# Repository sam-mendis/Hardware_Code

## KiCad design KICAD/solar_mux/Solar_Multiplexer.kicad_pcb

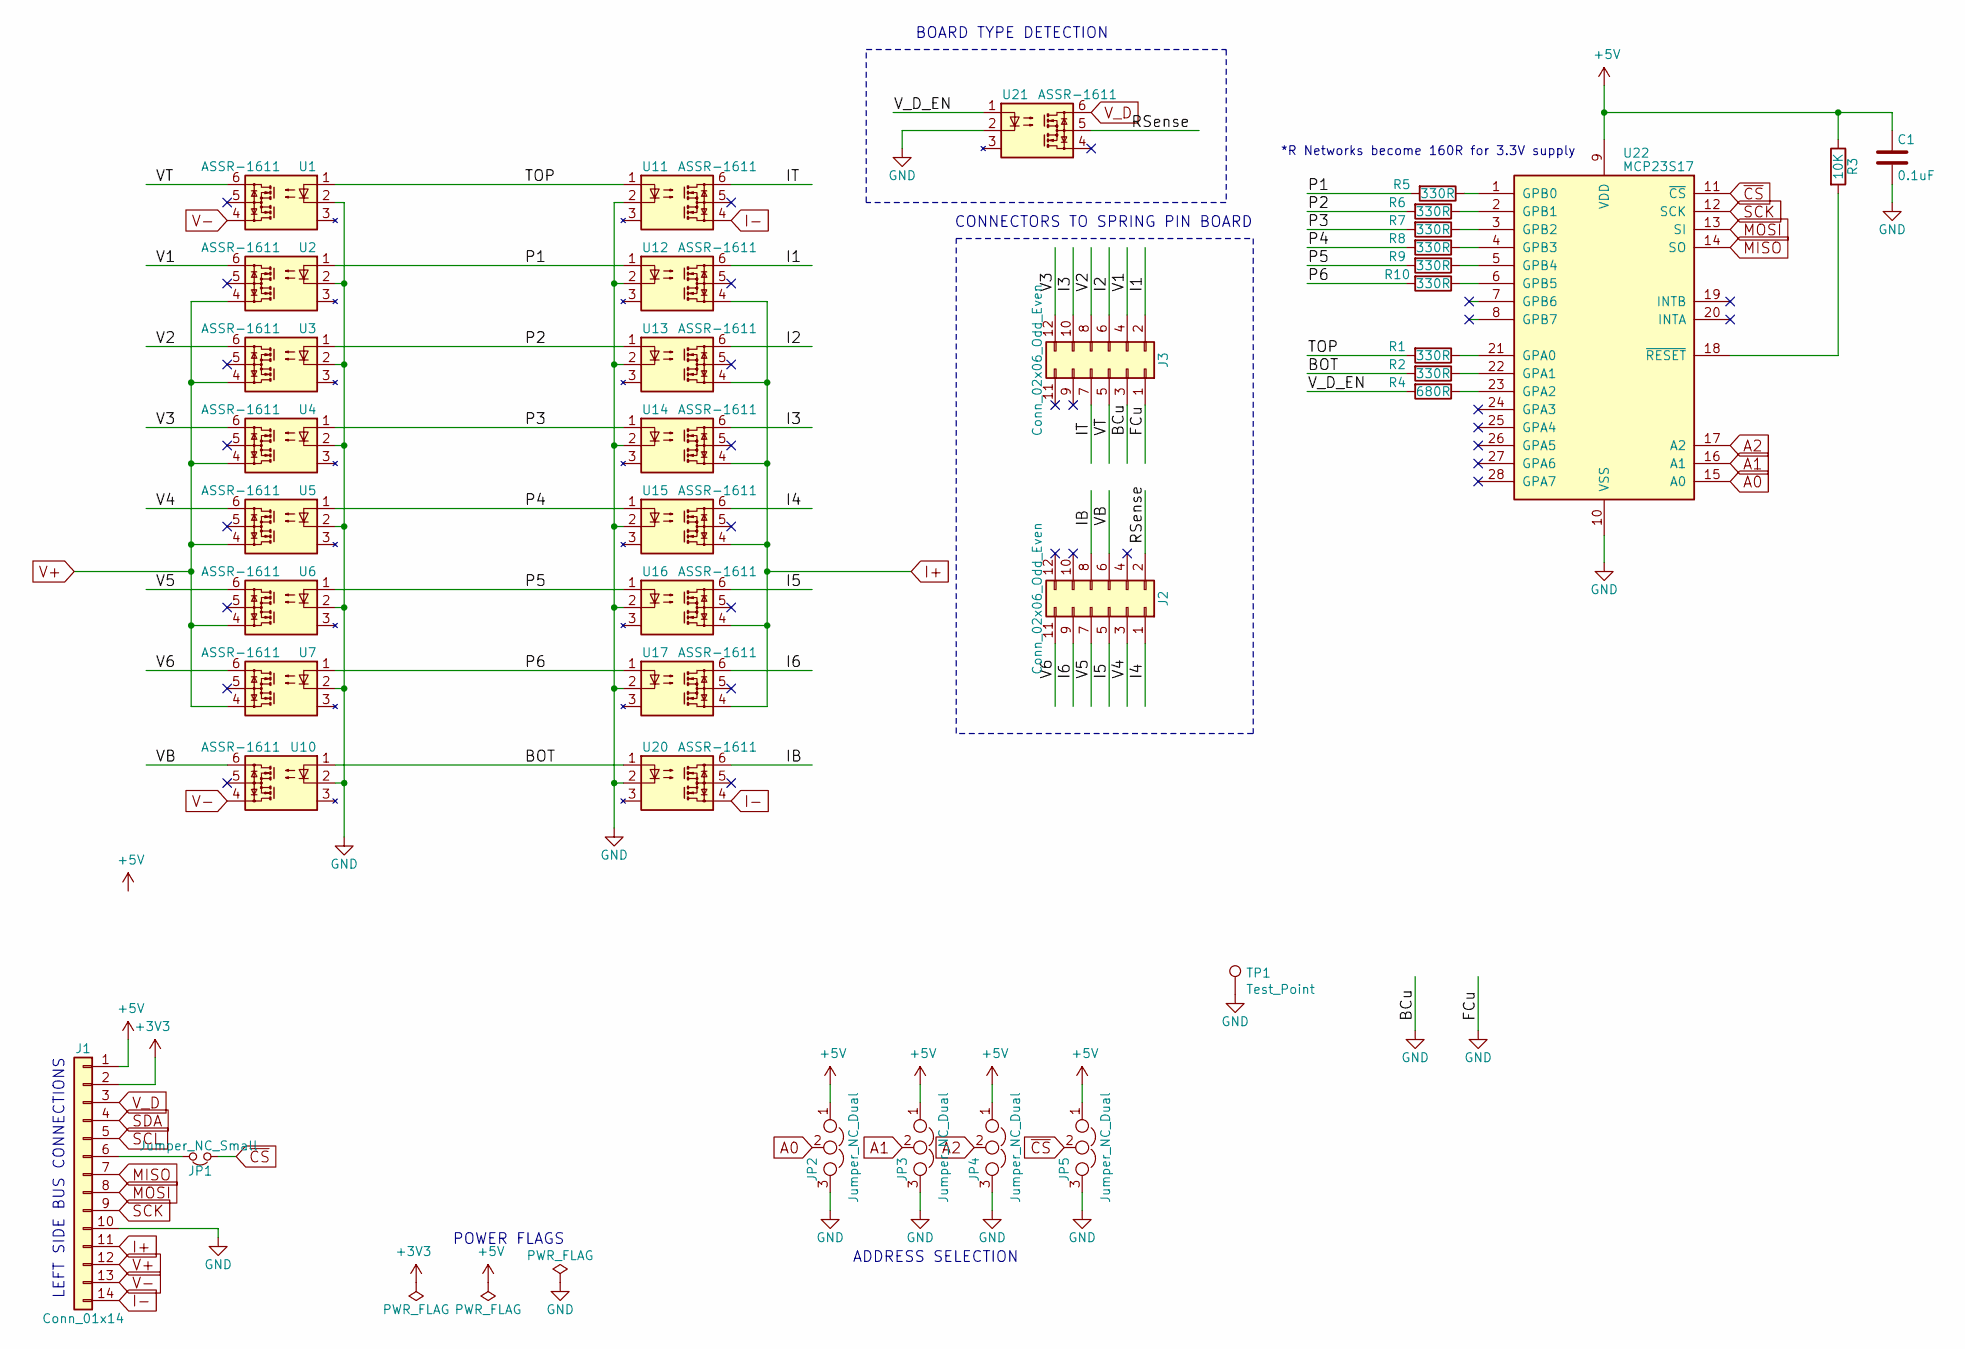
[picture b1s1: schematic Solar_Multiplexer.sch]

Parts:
C1: 0.1uF; CP_Radial_D8.0mm_P2.50mm; farnellCode 1759312
J1: Conn_01x14; PinHeader_1x14_P2.54mm_Vertical; farnellCode 2037821
J2: Conn_02x06_Odd_Even; PinHeader_2x06_P2.54mm_Vertical
J3: Conn_02x06_Odd_Even; PinHeader_2x06_P2.54mm_Vertical; FarnellPart 1930232
JP1: Jumper_NC_Small; SolderJumper-2_P1.3mm_Open_RoundedPad1.0x1.5mm
JP2, JP3, JP4, JP5: Jumper_NC_Dual; SolderJumper-3_P1.3mm_Open_RoundedPad1.0x1.5mm_NumberLabels
R1, R2, R5, R6, R7, R8, R9, R10: 330R; R_Axial_DIN0309_L9.0mm_D3.2mm_P15.24mm_Horizontal; farnellCode 2073607
R3: 10K; R_Axial_DIN0309_L9.0mm_D3.2mm_P15.24mm_Horizontal; farnellCode 2826357
R4: 680R; R_Axial_DIN0309_L9.0mm_D3.2mm_P15.24mm_Horizontal; farnellCode 2694489
TP1: Test_Point; TestPoint_Pad_2.5x2.5mm; farnell code 2293786
U1, U2, U3, U4, U5, U6, U7, U10, U11, U12, U13, U14, U15, U16, U17, U20, U21: ASSR-1611; DIP-6_W7.62mm; farnellCode 1708441
U22: MCP23S17; DIP-28_W7.62mm; farnellCode 1292238

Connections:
+3V3: J1.2
+5V: C1.1, J1.1, JP2.1, JP3.1, JP4.1, JP5.1, R3.1, U22.9 (VDD)
/BOT: R2.2, U10.1, U20.1
/I1: J3.2, U12.6
/I2: J3.6, U13.6
/I3: J3.10, U14.6
/I4: J2.1, U15.6
/I5: J2.5, U16.6
/I6: J2.9, U17.6
/IB: J2.8, U20.6
/IT: J3.7, U11.6
/P1: R5.2, U2.1, U12.1
/P2: R6.2, U3.1, U13.1
/P3: R7.2, U4.1, U14.1
/P4: R8.2, U5.1, U15.1
/P5: R9.2, U6.1, U16.1
/P6: R10.2, U7.1, U17.1
/RSense: J2.2, U21.5
/TOP: R1.2, U1.1, U11.1
/V1: J3.4, U2.6
/V2: J3.8, U3.6
/V3: J3.12, U4.6
/V4: J2.3, U5.6
/V5: J2.7, U6.6
/V6: J2.11, U7.6
/VB: J2.6, U10.6
/VT: J3.5, U1.6
/V_D_EN: R4.2, U21.1
A0: JP2.2, U22.15 (A0)
A1: JP3.2, U22.16 (A1)
A2: JP4.2, U22.17 (A2)
GND: C1.2, J1.10, J3.1, J3.3, JP2.3, JP3.3, JP4.3, JP5.3, TP1.1, U1.2, U2.2, U3.2, U4.2, U5.2, U6.2, U7.2, U10.2, U11.2, U12.2, U13.2, U14.2, U15.2, U16.2, U17.2, U20.2, U21.2, U22.10 (VSS)
I+: J1.11, U12.4, U13.4, U14.4, U15.4, U16.4, U17.4
I-: J1.14, U11.4, U20.4
MISO: J1.7, U22.14 (SO)
MOSI: J1.8, U22.13 (SI)
unnamed: J1.6, JP1.2
unnamed: R1.1, U22.21 (GPA0)
unnamed: R2.1, U22.22 (GPA1)
unnamed: R3.2, U22.18 (~RESET~)
unnamed: R4.1, U22.23 (GPA2)
unnamed: R5.1, U22.1 (GPB0)
unnamed: R6.1, U22.2 (GPB1)
unnamed: R7.1, U22.3 (GPB2)
unnamed: R8.1, U22.4 (GPB3)
unnamed: R9.1, U22.5 (GPB4)
unnamed: R10.1, U22.6 (GPB5)
SCK: J1.9, U22.12 (SCK)
SCL: J1.5
SDA: J1.4
V+: J1.12, U2.4, U3.4, U4.4, U5.4, U6.4, U7.4
V-: J1.13, U1.4, U10.4
V_D: J1.3, U21.6
~CS: JP1.1, JP5.2, U22.11 (~CS~)

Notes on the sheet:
ADDRESS SELECTION
POWER FLAGS
BOARD TYPE DETECTION
CONNECTORS TO SPRING PIN BOARD
LEFT SIDE BUS CONNECTIONS
*R Networks become 160R for 3.3V supply

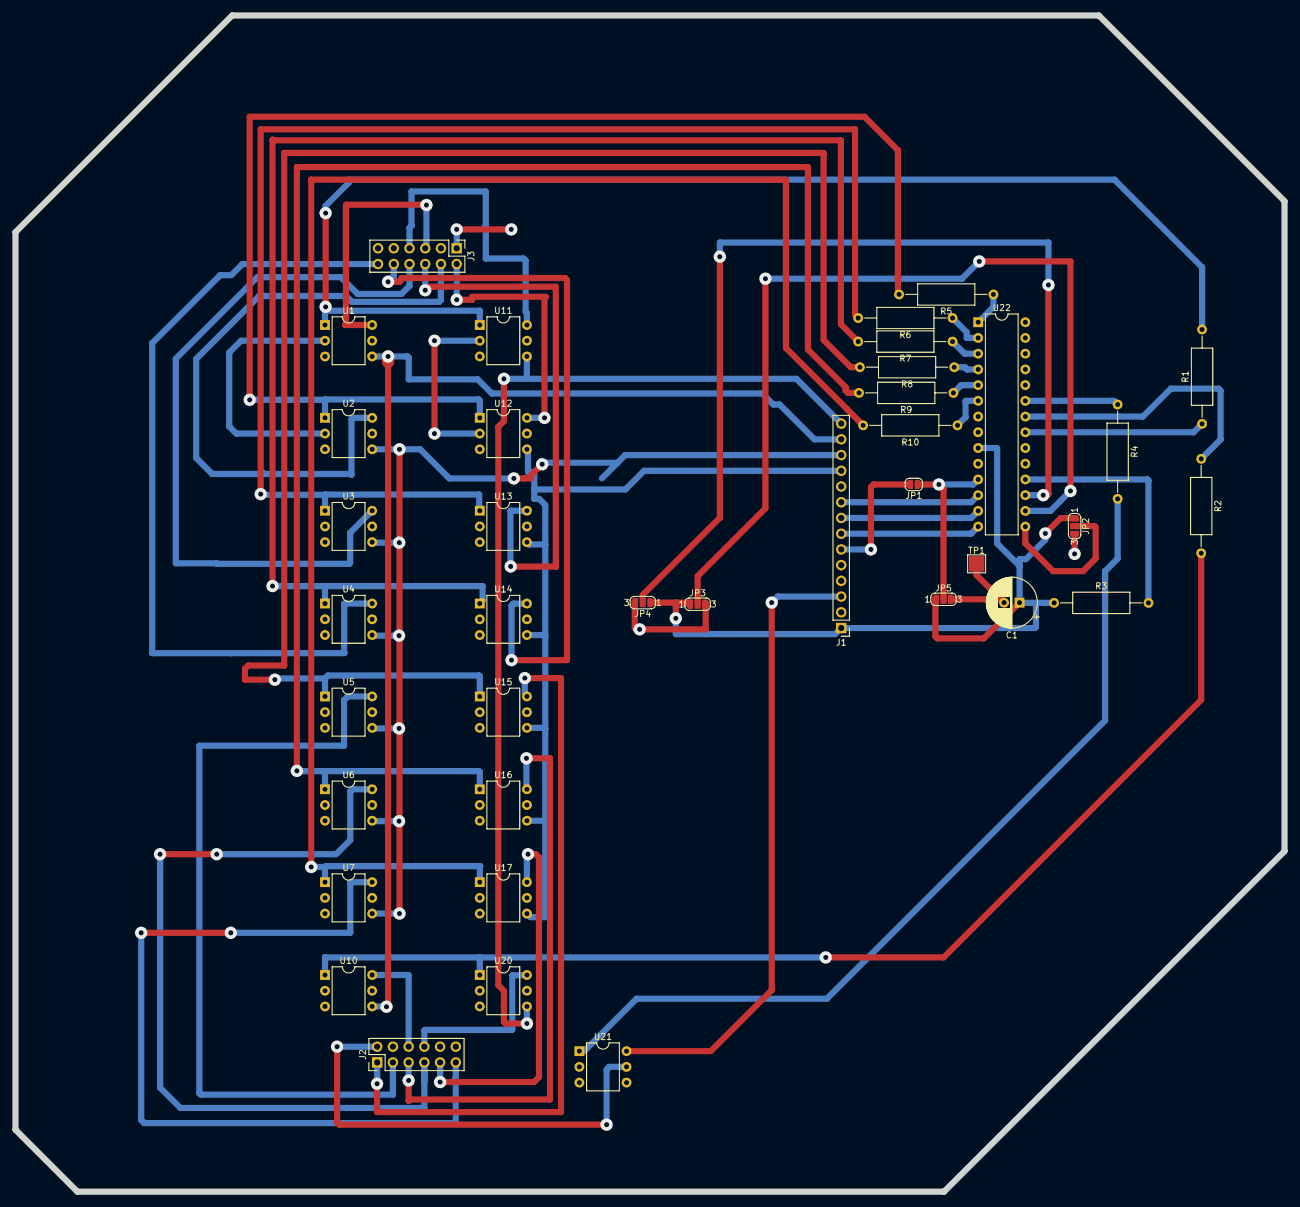
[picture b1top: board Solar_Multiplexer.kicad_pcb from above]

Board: 2 copper layers, 205.0 x 190.0 mm, 38 parts (0 on the bottom side), 51 nets.

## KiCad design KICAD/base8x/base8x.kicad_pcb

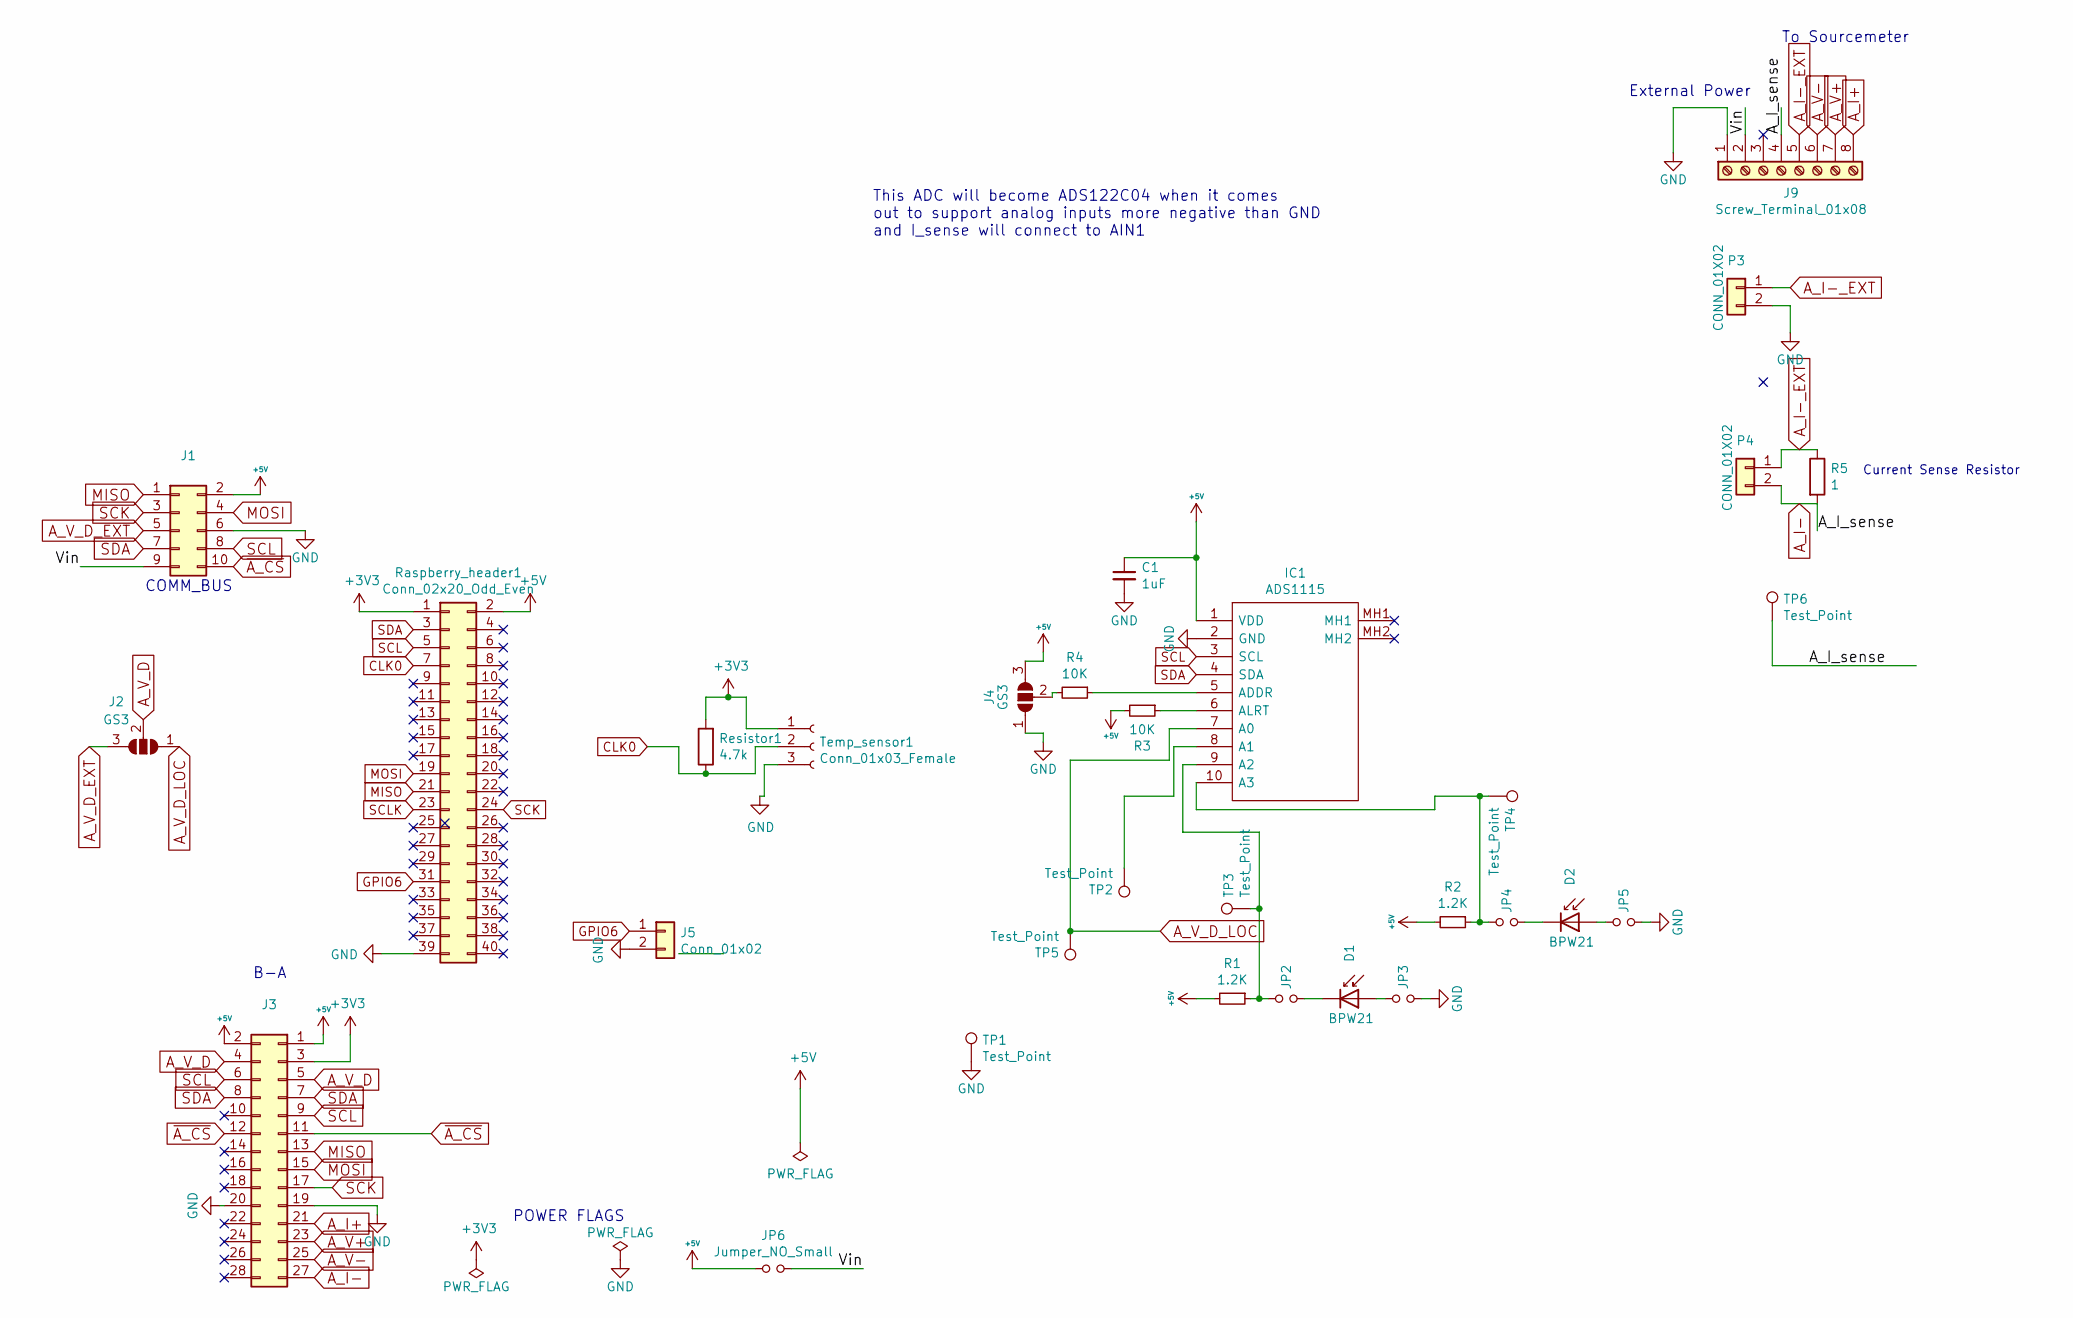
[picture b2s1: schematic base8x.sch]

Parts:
C1: 1uF; CP_Radial_D4.0mm_P1.50mm
D1, D2: BPW21; R_Axial_DIN0204_L3.6mm_D1.6mm_P7.62mm_Horizontal; farnellCode 1045427
IC1: ADS1115; Manufacturer_Part_Number ADS1115
J1: Conn_02x05_Odd_Even; IDC-Header_2x05_P2.54mm_Horizontal; farnellCode 2215290
J2, J4: GS3; SolderJumper-3_P1.3mm_Open_RoundedPad1.0x1.5mm_NumberLabels
J3: Conn_02x14_Counter_Clockwise; PinSocket_2x14_P2.54mm_Vertical
J5: Conn_01x02; PinHeader_1x02_P2.54mm_Vertical
J9: Screw_Terminal_01x08; PhoenixContact_MC_1,5_8-GF-3.5_1x08_P3.50mm_Horizontal_Thre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; farnellCode 2776340+1793014
JP2, JP3, JP4, JP5, JP6: Jumper_NO_Small; SolderJumper-2_P1.3mm_Open_RoundedPad1.0x1.5mm
P3, P4: CONN_01X02; PinHeader_1x02_P2.54mm_Vertical
R1, R2: 1.2K; R_Axial_DIN0516_L15.5mm_D5.0mm_P20.32mm_Horizontal; farnellCode 2073370
R3, R4: 10K; R_Axial_DIN0516_L15.5mm_D5.0mm_P20.32mm_Horizontal; farnellCode 2073607
R5: 1; R_Axial_DIN0516_L15.5mm_D5.0mm_P20.32mm_Horizontal; farnellCode 2663692
Raspberry_header1: Conn_02x20_Odd_Even; PinSocket_2x20_P2.54mm_Vertical
Resistor1: 4.7k; R_Axial_DIN0516_L15.5mm_D5.0mm_P20.32mm_Horizontal
TP1, TP2, TP3, TP4, TP5, TP6: Test_Point; TestPoint_Pad_2.5x2.5mm; farnellCode 2293786
Temp_sensor1: Conn_01x03_Female; PinSocket_1x03_P2.54mm_Vertical

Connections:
+3V3: J3.3, Raspberry_header1.1, Resistor1.2, Temp_sensor1.1
+5V: C1.1, IC1.1 (VDD), J1.2, J3.1, J3.2, J4.3 (B), JP6.1, R1.2, R2.2, R3.2, Raspberry_header1.2
/Vin: J1.9, J9.2, JP6.2
A_I+: J3.21, J9.8
A_I-: J3.27, J9.4, P4.2, R5.2, TP6.1
A_I-_EXT: J9.5, P3.1, P4.1, R5.1
A_V+: J3.23, J9.7
A_V-: J3.25, J9.6
A_V_D: J2.2 (C), J3.4, J3.5
A_V_D_EXT: J1.5, J2.3 (B)
A_V_D_LOC: IC1.7 (A0), J2.1 (A), TP5.1
CLK0: Raspberry_header1.7, Resistor1.1, Temp_sensor1.2
GND: C1.2, IC1.2 (GND), J1.6, J3.19, J3.20, J4.1 (A), J5.2, J9.1, JP3.2, JP5.2, P3.2, Raspberry_header1.39, TP1.1, Temp_sensor1.3
GPIO6: J5.1, Raspberry_header1.31
MISO: J1.1, J3.13, Raspberry_header1.21
MOSI: J1.4, J3.15, Raspberry_header1.19
unnamed: D1.1 (K), JP2.2
unnamed: D1.2 (A), JP3.1
unnamed: D2.1 (K), JP4.2
unnamed: D2.2 (A), JP5.1
unnamed: IC1.5 (ADDR), R4.1
unnamed: IC1.6 (ALRT), R3.1
unnamed: IC1.8 (A1), TP2.1
unnamed: IC1.9 (A2), JP2.1, R1.1, TP3.1
unnamed: IC1.10 (A3), JP4.1, R2.1, TP4.1
unnamed: J4.2 (C), R4.2
SCK: J1.3, J3.17, Raspberry_header1.24
SCL: IC1.3 (SCL), J1.8, J3.6, J3.9, Raspberry_header1.5
SCLK: Raspberry_header1.23
SDA: IC1.4 (SDA), J1.7, J3.7, J3.8, Raspberry_header1.3
~A_CS: J1.10, J3.11, J3.12

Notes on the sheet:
POWER FLAGS
B-A
COMM_BUS
To Sourcemeter
External Power
Current Sense Resistor
This ADC will become ADS122C04 when it comes out to support analog inputs more negative than GND and I_sense will connect to AIN1

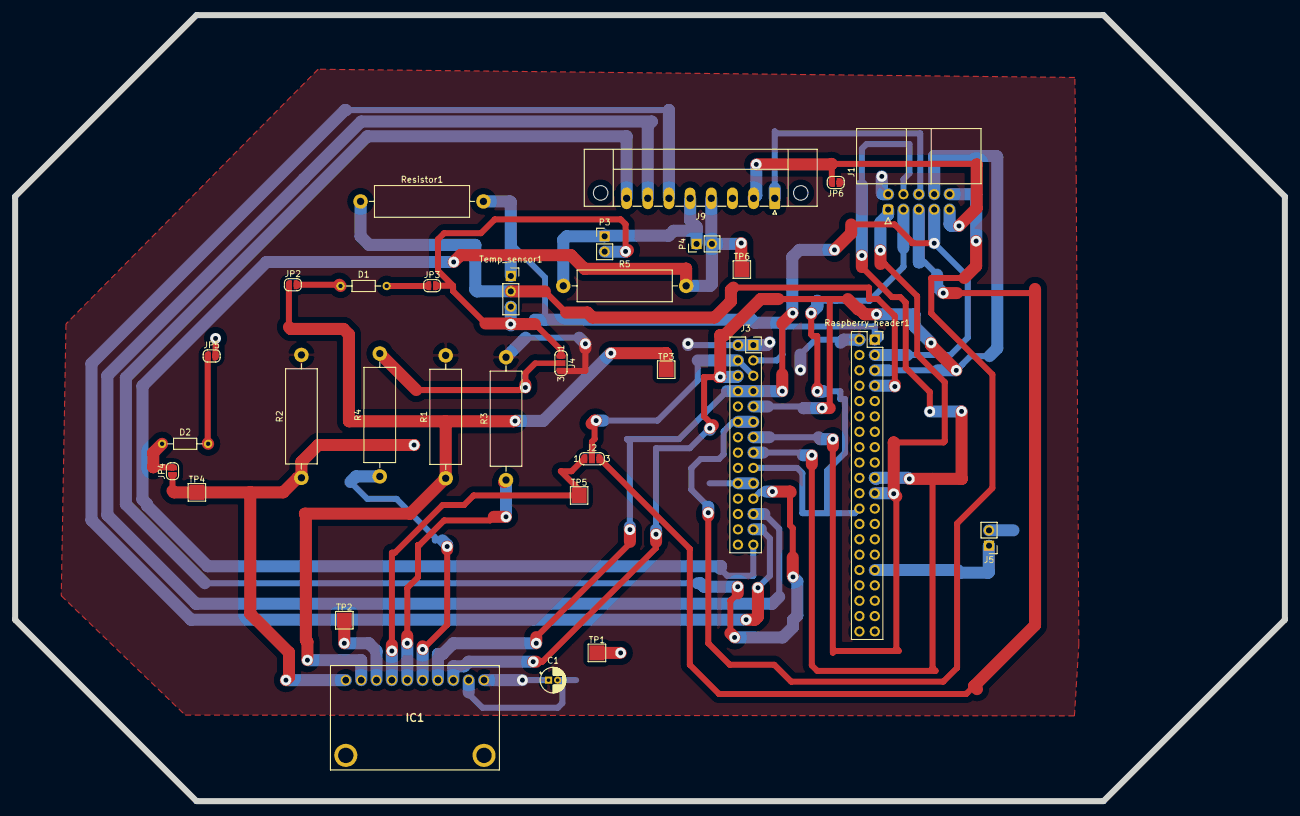
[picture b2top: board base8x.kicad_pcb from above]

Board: 4 copper layers, 210.0 x 130.0 mm, 31 parts (0 on the bottom side), 30 nets.

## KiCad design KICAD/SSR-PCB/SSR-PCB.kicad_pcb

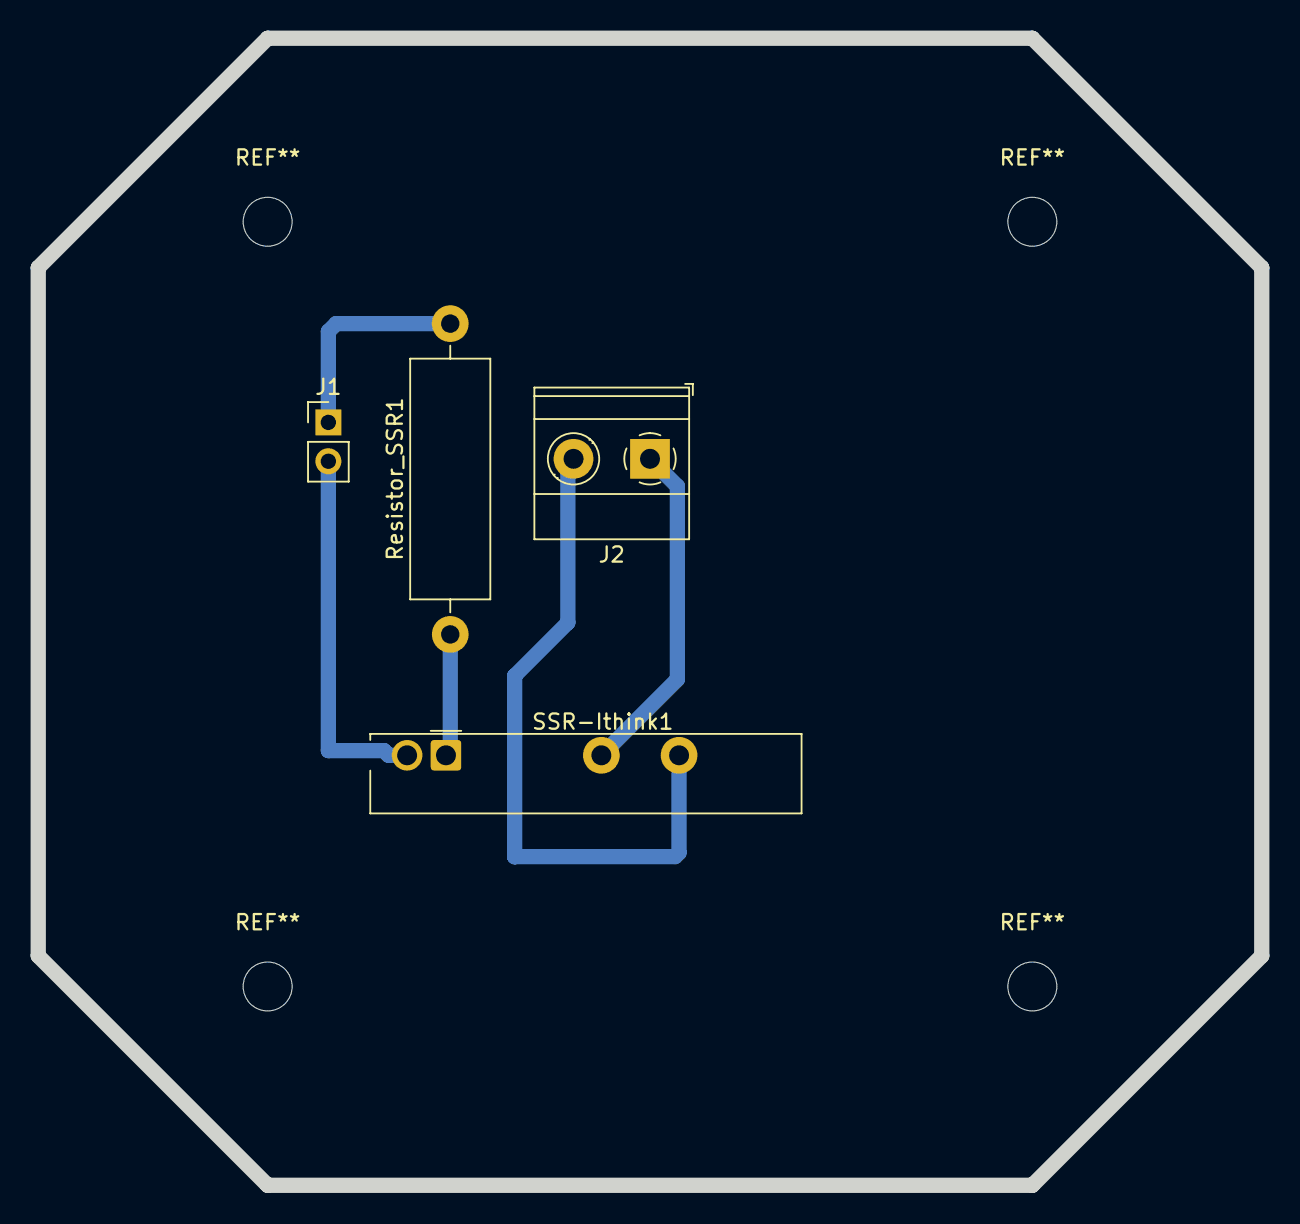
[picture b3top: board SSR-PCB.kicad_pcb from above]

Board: 4 copper layers, 80.0 x 75.0 mm, 4 parts (0 on the bottom side), 5 nets.

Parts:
J1: Conn_01x02; PinHeader_1x02_P2.54mm_Vertical
J2: Screw_Terminal_01x02; TerminalBlock_Phoenix_MKDS-1,5-2_1x02_P5.00mm_Horizontal
Resistor_SSR1: ?; R_Axial_DIN0516_L15.5mm_D5.0mm_P20.32mm_Horizontal
SSR-Ithink1: 34.81-7048; Finder_34.81

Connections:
GND: J1.2, SSR-Ithink1.A2
GPIO6: J1.1, Resistor_SSR1.2
unnamed: J2.1, SSR-Ithink1.11
unnamed: J2.2, SSR-Ithink1.14
unnamed: Resistor_SSR1.1, SSR-Ithink1.A1

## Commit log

2021-02-24 Adding all OpenSCAD Models
2021-02-24 Cleaning up and adding KiCad Code
2021-02-25 Chanign track sizes and re producing drill files
2021-02-26 updates for screw
2021-03-01 Creating models for 3D printing
2021-03-02 Important changes
2021-03-09 KiCAD edits
2021-03-11 Changing Via sizes and track widths
2021-04-07 edits to substrate holder
